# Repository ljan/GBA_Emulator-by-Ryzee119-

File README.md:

# GBA RaspberryPi Zero  

## Display:  
https://sudomod.com/forum/viewtopic.php?f=22&t=2312  
https://sudomod.com/forum/viewtopic.php?f=25&t=5614  
https://sudomod.com/forum/viewtopic.php?f=22&t=5854&p=60773#p60709  
https://learn.adafruit.com/adafruit-2-8-pitft-capacitive-touch/downloads  

Screen | Raspberry Pi 3 or zero 
------------ | -------------
SDI(MOSI) | Pin 19 (GPIO10) 
SDO(MISO) | PIN 21 (GPIO9) 
SCK | Pin 23 (GPIO11) 
CS | Pin 24 (GPIO8) 
DC | Pin 22 (GPIO25) 
RESET | Pin 26 (GPIO7) 
LED | Pin 12 (GPIO18) 
VCC | Pin 1 (3.3V) 
GND | Pin 20 (GND) 

## Audio:  
http://www.ti.com/lit/ds/symlink/lm4875.pdf  

## Power:  
https://hackaday.io/project/19035-zerophone-a-raspberry-pi-smartphone/log/69596-a-guide-on-powering-pi-zero-directly-from-liion-batteries  

## Credits:  
> This was originally designed by /u/Ryzee
> Originally posted on Reddit here:
> https://www.reddit.com/r/DIY/comments/4zbqwr/this_is_my_attempt_at_making_a_portable_emulator/
> 
> Build Photos:
> http://imgur.com/a/kjFmS
> 
> I am releasing these design files in good faith that people will use them to learn something about electronics and maybe bring > an old Gameboy Advance (GBA) back to life.
> 
> I don’t want to see people taking this design and knocking it off for a quick buck.
> If you don’t want to deal with all this work another redditor /u/Flav0r has designed something quite similar to this. http://gamepieadvance.com/ I understand he may be working on DIY Kits.

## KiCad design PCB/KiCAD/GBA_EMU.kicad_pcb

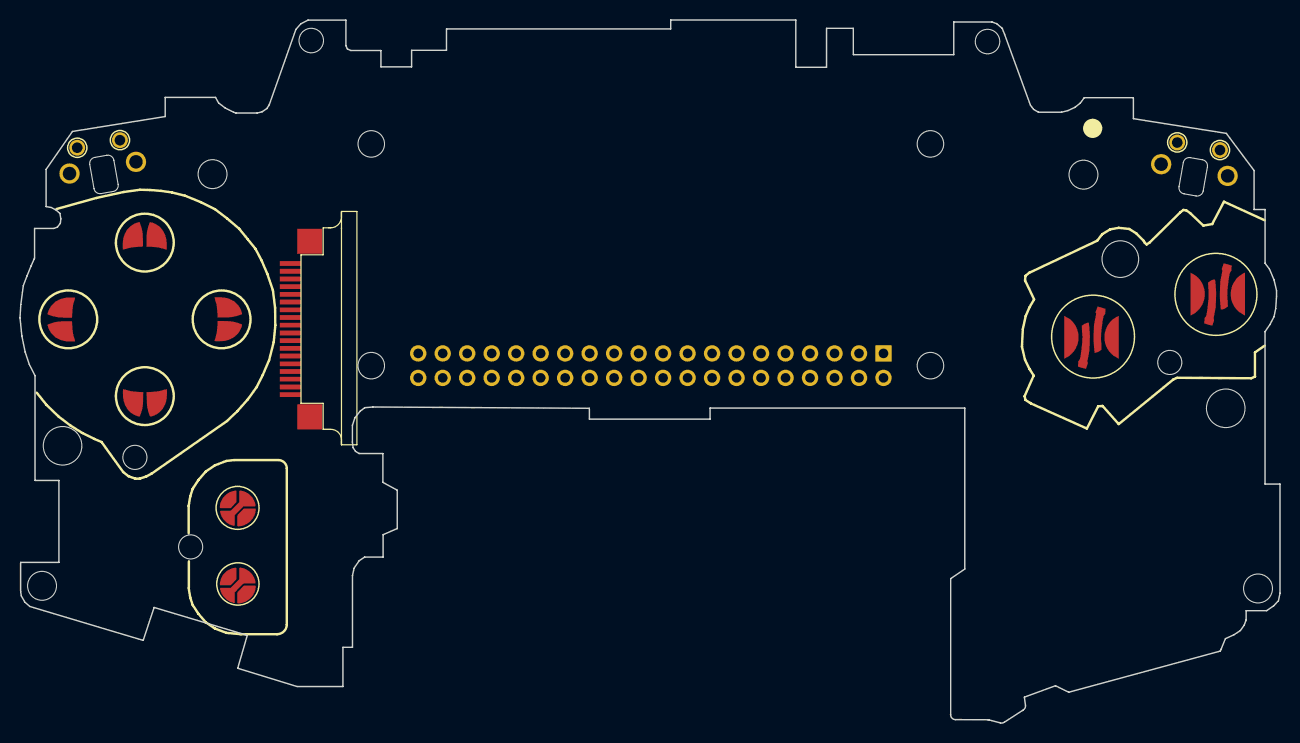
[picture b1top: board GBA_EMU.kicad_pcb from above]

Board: 2 copper layers, 130.7 x 72.9 mm, 19 parts (0 on the bottom side), 9 nets, no tracks yet.

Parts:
@HOLE0, @HOLE1, @HOLE2, @HOLE3, @HOLE4, @HOLE5, @HOLE6, @HOLE7, @HOLE8, @HOLE9, @HOLE10, @HOLE11: (no value)
J1: Raspberry_Pi_2_3; Raspberry_Pi_Zero_Socketed_THT_FaceDown_MountingHoles
SW_AB1: SW_DIP_x02; AB_BUTTON
SW_DPAD1: SW_DIP_x04; D-PAD
SW_L1: SW_DIP_x01; SHOULDER_BUTTON
SW_R1: SW_DIP_x01; SHOULDER_BUTTON
SW_SS1: SW_DIP_x02; START_SELECT_BUTTON
U1: ILI3941; 18PIN-0.8MM

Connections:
+3V3: J1.1, J1.17, U1.9
+5V: J1.2, J1.4, U1.10
GND: J1.6, J1.9, J1.14, J1.20, J1.25, J1.30, J1.34, J1.39, SW_AB1.3, SW_AB1.4, SW_DPAD1.5, SW_DPAD1.6, SW_DPAD1.7, SW_DPAD1.8, SW_L1.2, SW_R1.2, SW_SS1.3, SW_SS1.4, U1.1, U1.8
TFT_CS: J1.24, U1.5
TFT_DC: J1.18, U1.4
TFT_MISO: J1.21, U1.7
TFT_MOSI: J1.19, U1.6
TFT_RESET: J1.22, U1.2
TFT_SCK: J1.23, U1.3

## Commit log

2019-03-31 reorganisiert
    moved files in seperate folders
2019-04-04 cleaned pcb and schematic
    keept outlines of pcb and onyl some parts
2019-04-05 cleaned pcb
    removed most parts and marked positions
2019-04-05 converted to KiCAD
2019-04-10 gitignore
    copied from https://github.com/github/gitignore
2019-04-10 Imported Foodprints
    Button Foodprints from https://github.com/AEFeinstein/gbaZero
2019-04-10 imported footprints
    button footprints from https://github.com/AEFeinstein/gbaZero
2019-04-11 Create .gitignore
    template for eagle and kicad
2019-04-14 LCD Connection
    https://github.com/juj/fbcp-ili9341#if-you-wired-the-display-to-the-pi-yourself
    https://sudomod.com/forum/viewtopic.php?f=22&t=5854
    Screen<------------>Raspberry Pi 3 or zero
    LED<-------------->Pin 12 (GPIO18)
    SCK<-------------->Pin 23 (GPIO11)
    SDI(MOSI)<----->Pin 19 (GPIO10)
2019-04-14 PWM Audio
2019-04-19 LCD Pins
2019-05-01 Audio, LCD, Buttons
